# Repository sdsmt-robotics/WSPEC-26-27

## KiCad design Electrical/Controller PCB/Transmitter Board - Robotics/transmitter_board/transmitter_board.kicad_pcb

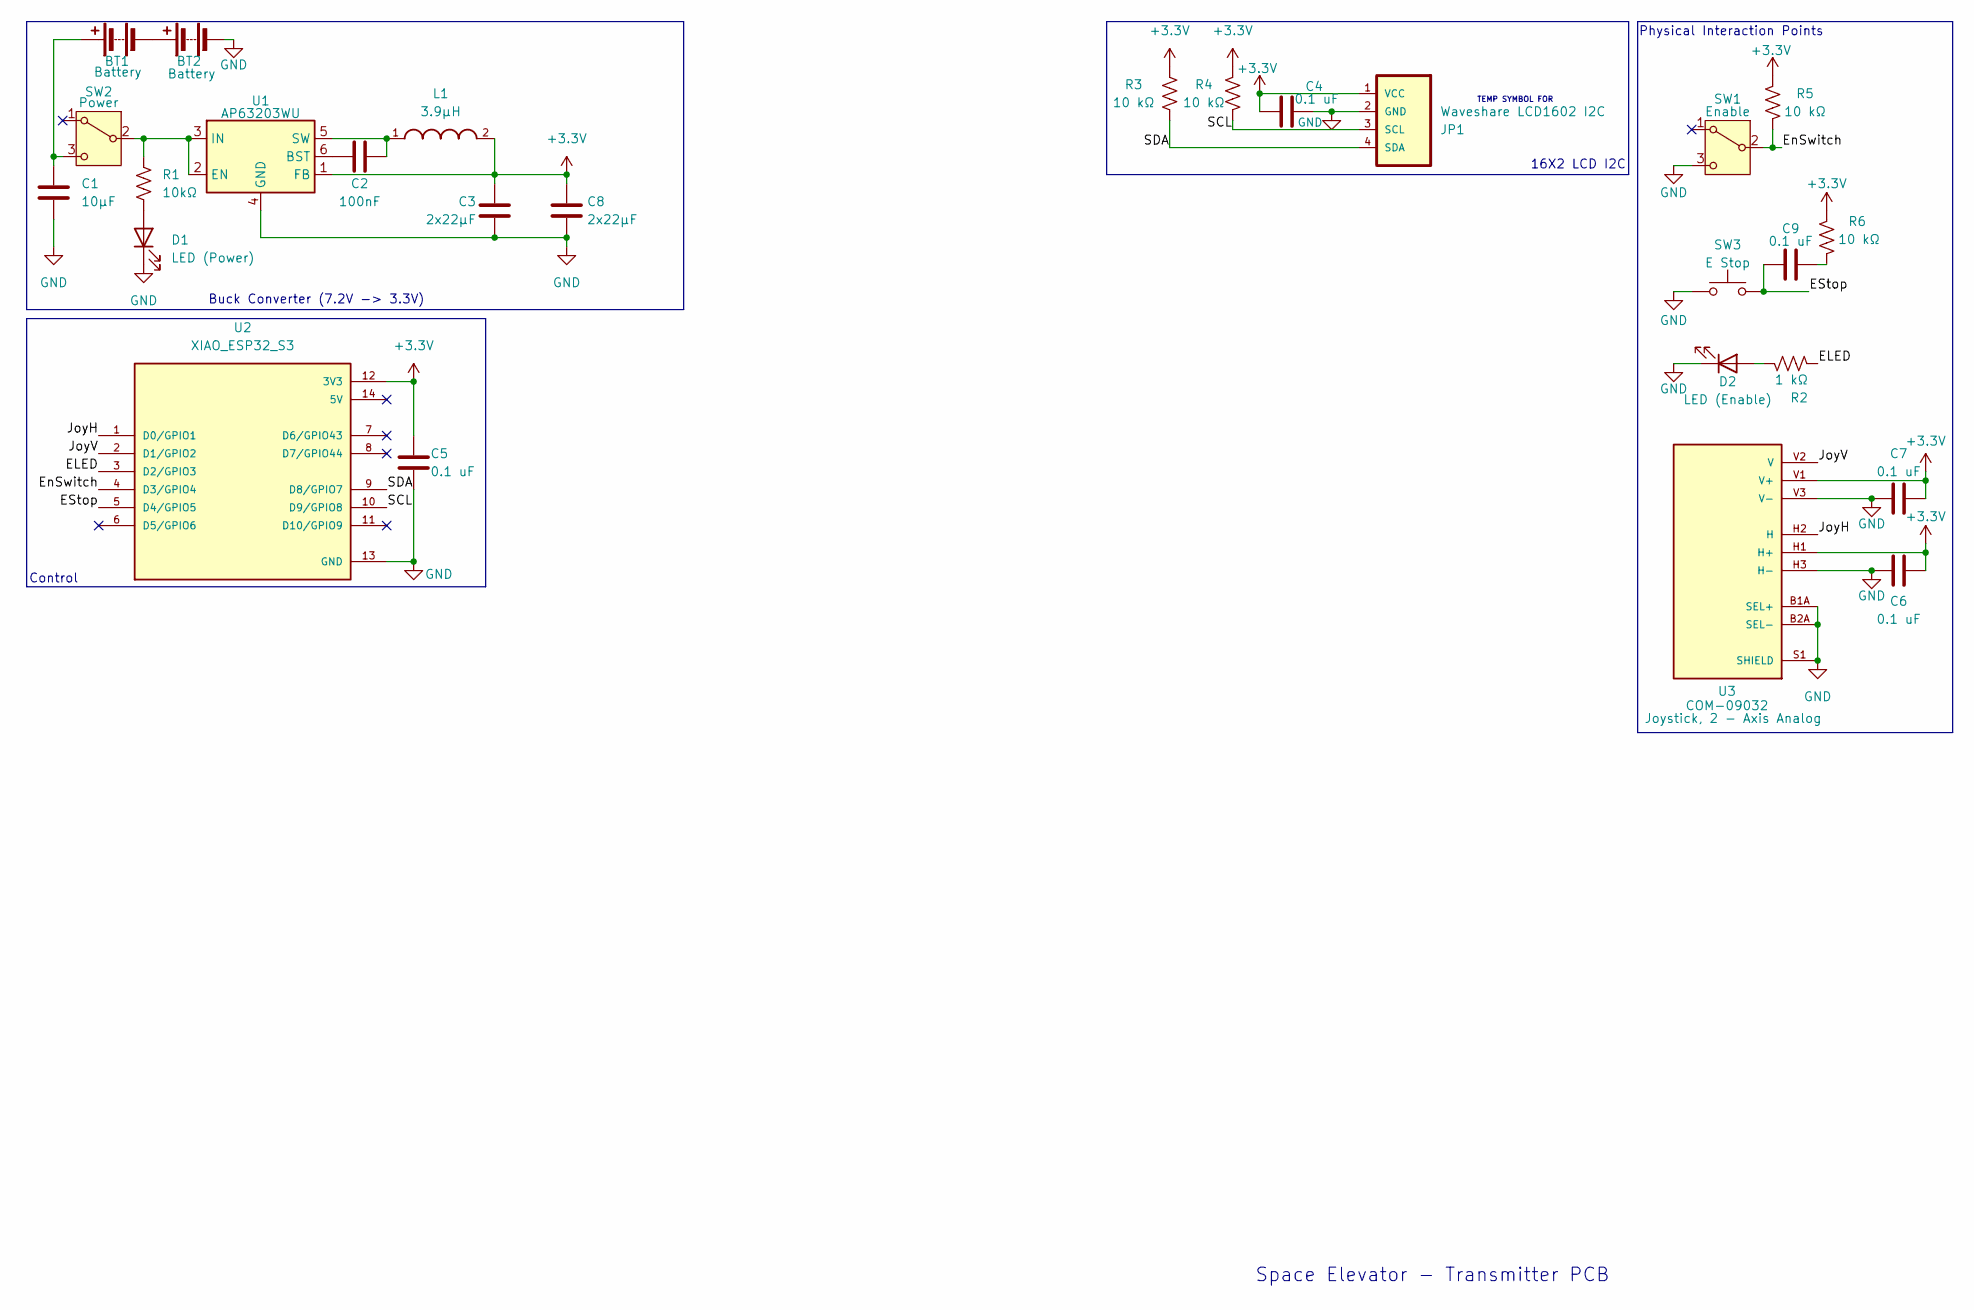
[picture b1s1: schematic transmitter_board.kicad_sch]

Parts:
BT1, BT2: Battery; BatteryHolder_Keystone_1042_1x18650
C1: 10µF; C_0805_2012Metric
C2: 100nF; C_0805_2012Metric
C3, C8: 2x22µF; C_0805_2012Metric
C4, C5, C6, C7, C9: 0.1 uF; C_0805_2012Metric
D1: LED (Power); LED_D4.0mm
D2: LED (Enable); LED_D4.0mm
JP1: Waveshare LCD1602 I2C; JST_PH_S4B-PH-K_1x04_P2.00mm_Horizontal
L1: 3.9µH; INDC0603X33N; DigiKey_Part_Number 490-6730-1-ND
R1: 10kΩ; R_0805_2012Metric
R2: 1 kΩ; R_0805_2012Metric
R3, R4, R5, R6: 10 kΩ; R_0805_2012Metric
SW1: Enable; SS12SDP2_NKK
SW2: Power; SS12SDP2_NKK
SW3: E Stop; SW_800AWSP9M2QE
U1: AP63203WU; TSOT-23-6
U2: XIAO_ESP32_S3; MODULE_XIAO_ESP32_S3; PARTREV April 22nd, 2026
U3: COM-09032; XDCR_COM-09032; PARTREV N/A

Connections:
+3.3V: C3.1, C4.1, C5.1, C6.2, C7.2, C8.1, JP1.1 (VCC), L1.2, R3.2, R4.1, R5.2, R6.2, U1.1 (FB), U2.12 (3V3), U3.H1 (H+), U3.V1 (V+)
/ELED: R2.2, U2.3 (D2/GPIO3)
/EStop: C9.1, SW3.2, U2.5 (D4/GPIO5)
/EnSwitch: R5.1, SW1.2 (B), U2.4 (D3/GPIO4)
/JoyH: U2.1 (D0/GPIO1), U3.H2 (H)
/JoyV: U2.2 (D1/GPIO2), U3.V2 (V)
/SCL: JP1.3 (SCL), R4.2, U2.10 (D9/GPIO8)
/SDA: JP1.4 (SDA), R3.1, U2.9 (D8/GPIO7)
GND: BT2.2 (-), C1.2, C3.2, C4.2, C5.2, C6.1, C7.1, C8.2, D1.1 (K), D2.1 (K), JP1.2 (GND), SW1.3 (C), SW3.1, U1.4 (GND), U2.13 (GND), U3.B1A (SEL+), U3.B2A (SEL-), U3.H3 (H-), U3.S1 (SHIELD), U3.S2 (SHIELD), U3.S3 (SHIELD), U3.S4 (SHIELD), U3.V3 (V-)
unnamed: BT1.1 (+), C1.1, SW2.3 (C)
unnamed: BT1.2 (-), BT2.1 (+)
unnamed: C9.2, R6.1
unnamed: D1.2 (A), R1.2
unnamed: D2.2 (A), R2.1
unnamed: R1.1, SW2.2 (B), U1.2 (EN), U1.3 (IN)
unnamed: C2.1, U1.6 (BST)
unnamed: C2.2, L1.1, U1.5 (SW)

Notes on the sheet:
Physical Interaction Points
16X2 LCD I2C
Buck Converter (7.2V -> 3.3V)
TEMP SYMBOL FOR
Space Elevator - Transmitter PCB
Control

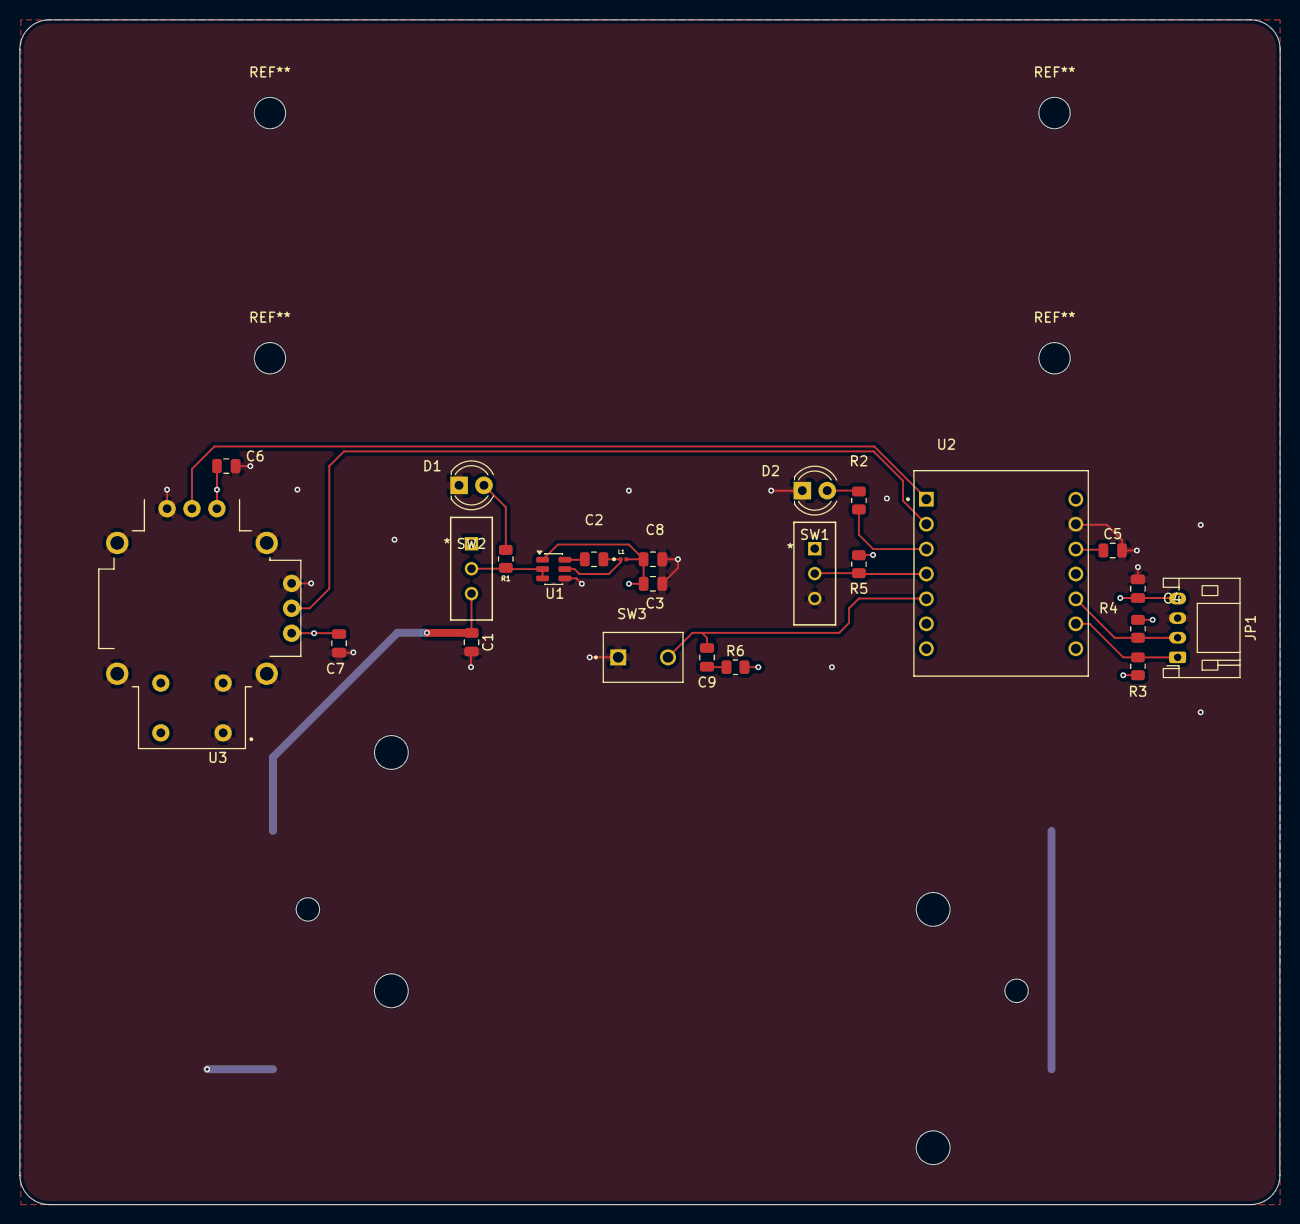
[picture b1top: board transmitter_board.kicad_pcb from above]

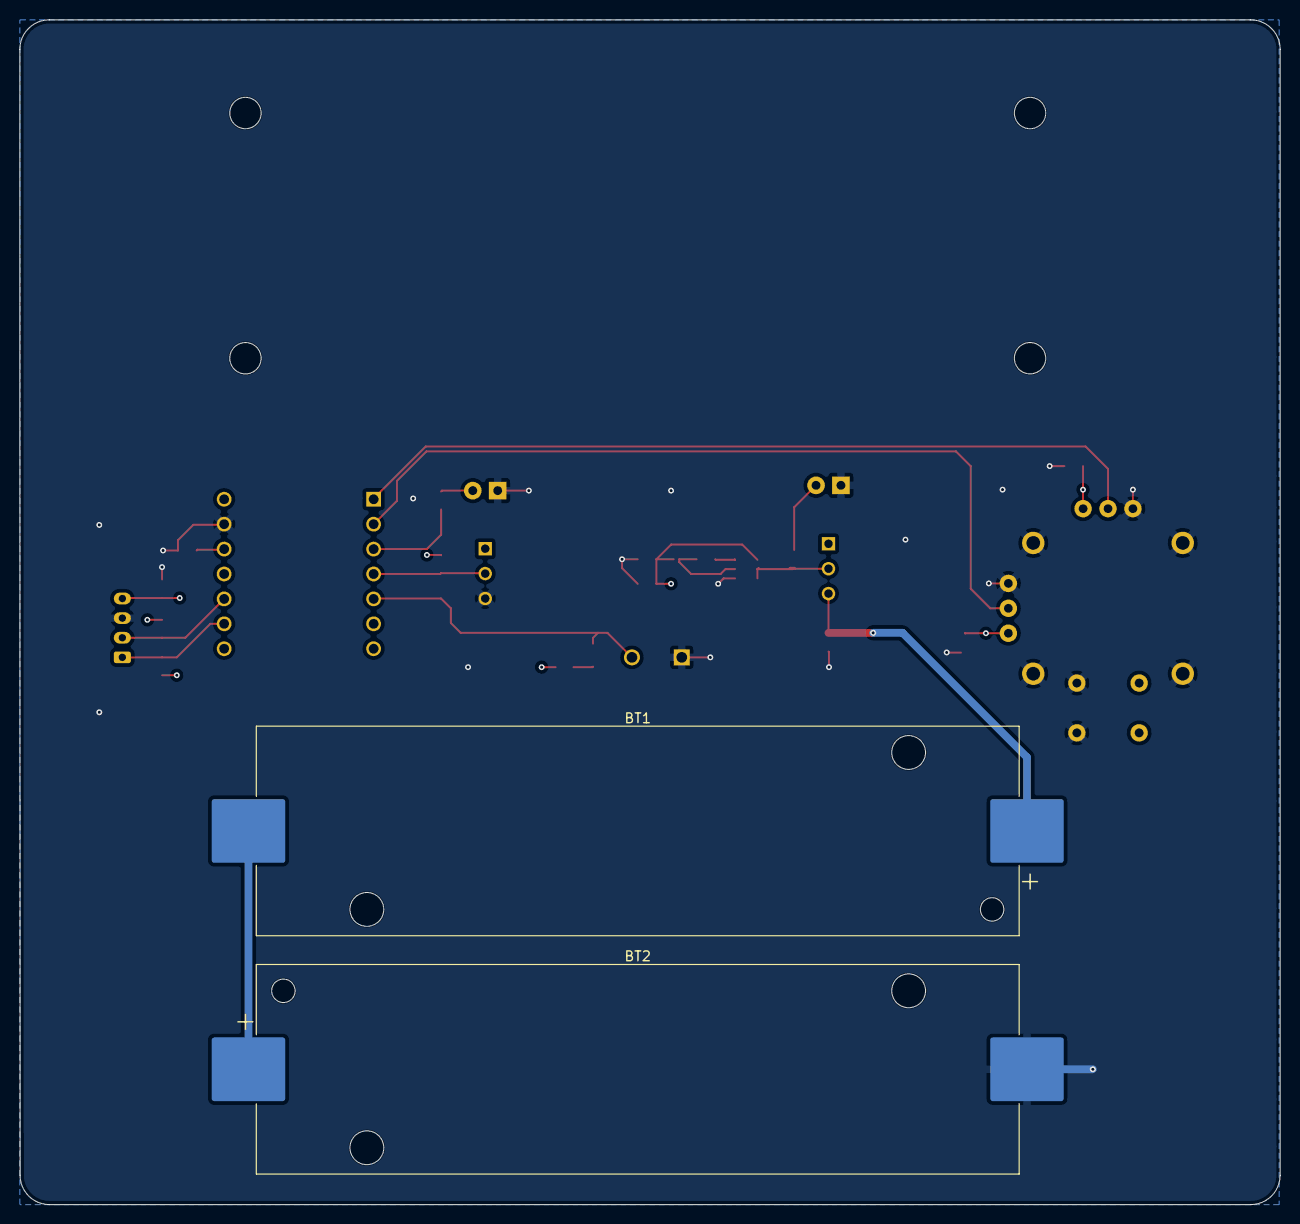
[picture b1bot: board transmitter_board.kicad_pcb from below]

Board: 4 copper layers, 128.5 x 120.8 mm, 27 parts (2 on the bottom side), 17 nets.

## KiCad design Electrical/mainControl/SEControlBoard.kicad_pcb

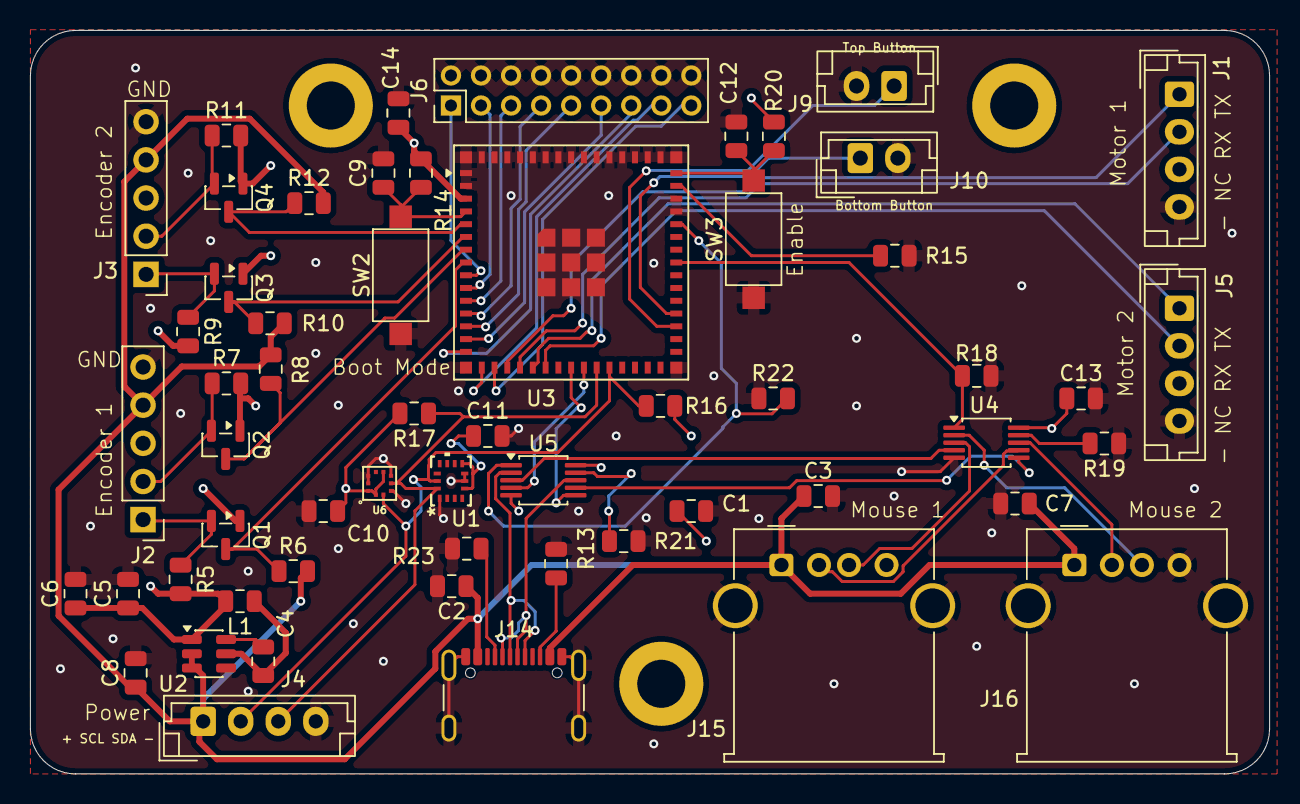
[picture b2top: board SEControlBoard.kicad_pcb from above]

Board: 4 copper layers, 82.5 x 49.5 mm, 57 parts (0 on the bottom side), 49 nets.

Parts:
C1, C2, C3, C4, C7, C8, C9, C10, C11, C12, C13, C14: 100nF; C_0805_2012Metric
C5, C6: 22uF; C_0805_2012Metric
J1, J4, J5: Conn_01x04; JST_EH_B4B-EH-A_1x04_P2.50mm_Vertical
J2: Encoder 1; PinHeader_1x05_P2.54mm_Vertical
J3: Encoder 2; PinHeader_1x05_P2.54mm_Vertical
J6: Conn_02x09_Odd_Even; PinHeader_2x09_P2.00mm_Vertical
J9: TopButton; JST_EH_B2B-EH-A_1x02_P2.50mm_Vertical
J10: BtottomButton; JST_EH_B2B-EH-A_1x02_P2.50mm_Vertical
J14: USB_C_Receptacle_USB2.0_16P; USB_C_Receptacle_GCT_USB4105-xx-A_16P_TopMnt_Horizontal
J15, J16: USB_A; USB_A_Molex_67643_Horizontal
L1: 4.7uH; C_0805_2012Metric
Q1, Q2, Q3, Q4: BSS138; SOT-23
R5, R6, R7, R8, R9, R10, R11, R12, R14, R15, R16, R17, R18, R19, R20, R21, R22: 10k; C_0805_2012Metric
R13, R23: 5.1k; C_0805_2012Metric
SW2, SW3: SW_MEC_5G; SW_SPST_CK_RS282G05A3
U1: BMI323; BMI323_BOS
U2: AP63203WU; TSOT-23-6
U3: ESP32-S3-MINI-1U; ESP32-S2-MINI-1U
U4, U5: TS3USB30EDGSR; TSSOP-10_3x3mm_P0.5mm
U6: BMP384; LGA-10

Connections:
+3.3V: C1.1, C5.1, C6.1, C10.1, C11.1, C13.1, C14.1, L1.2, Q1.1 (G), Q2.1 (G), Q3.1 (G), Q4.1 (G), R5.2, R7.2, R9.2, R11.2, R14.2, R16.2, R17.2, R20.2, U1.5 (VDDIO), U1.8 (VDD), U2.1 (FB), U3.3 (3V3), U4.10 (VCC), U5.10 (VCC), U6.1 (VDDIO), U6.6 (CSB), U6.10 (VDD)
+5V: C2.1, C3.1, C7.1, C8.1, J2.4, J3.4, J4.1, J14.A4 (VBUS), J14.A9 (VBUS), J14.B4 (VBUS), J14.B9 (VBUS), J15.1 (VBUS), J16.1 (VBUS), R6.2, R8.2, R10.2, R12.2, U2.2 (EN), U2.3 (IN)
/BO_1: J6.1, U3.9 (IO5)
/BO_2: J6.3, U3.10 (IO6)
/BO_3: J6.5, U3.11 (IO7)
/BO_4: J6.7, U3.12 (IO8)
/BO_5: J6.9, U3.13 (IO9)
/BO_6: J6.11, U3.14 (IO10)
/BO_7: J6.13, U3.15 (IO11)
/BO_8: J6.15, U3.16 (IO12)
/BO_9: J6.17, U3.17 (IO13)
/Bottom Button: J10.1, U3.34 (IO38)
/E1OutA: J2.2, Q2.2 (S), R7.1
/E1Outb: J2.1, Q1.2 (S), R5.1
/E1OutbL: Q1.3 (D), R6.1, U3.8 (IO4)
/E2OutA: J3.2, Q4.2 (S), R11.1
/E2Outb: J3.1, Q3.2 (S), R9.1
/E2OutbL: Q3.3 (D), R10.1, U3.6 (IO2)
/E3OutbL: Q2.3 (D), R8.1, U3.7 (IO3)
/E4OutbL: Q4.3 (D), R12.1, U3.5 (IO1)
/M1_RX: J1.1, U3.18 (IO14)
/M1_TX: J1.2, U3.19 (IO15)
/M2_RX: J5.1, U3.20 (IO16)
/M2_TX: J5.2, U3.21 (IO17)
/Tob Button: J9.1, U3.33 (IO37)
/USBSel1: R18.2, U3.38 (IO42), U4.1 (S)
/USBSel2: R22.2, U3.41 (IO45), U5.1 (S)
/USBo1+: U4.4 (D+), U5.3 (D2+)
/USBo1-: U4.6 (D-), U5.7 (D2-)
/USBo+: U3.24 (USB_D+), U5.4 (D+)
/USBo-: U3.23 (USB_D-), U5.6 (D-)
/espBoot: C9.1, R14.1, SW2.2 (B), U3.4 (IO0)
/espEn: C12.1, R20.1, SW3.2 (B), U3.45 (EN)
/scl: J4.2, R16.1, U1.13 (SCX), U3.26 (IO26), U6.2 (SCK/SCL)
/sda: J4.3, R17.1, U1.14 (SDX), U3.25 (IO21), U6.4 (SDI/SDA)
/usb1_+: J16.3 (D+), U4.2 (D1+)
/usb1_-: J16.2 (D-), U4.8 (D1-)
/usb2_+: J15.3 (D+), U4.3 (D2+)
/usb2_-: J15.2 (D-), U4.7 (D2-)
/usb3_+: J14.A6 (D+), J14.B6 (D+), U5.2 (D1+)
/usb3_-: J14.A7 (D-), J14.B7 (D-), U5.8 (D1-)
GND: C1.2, C2.2, C3.2, C5.2, C6.2, C7.2, C8.2, C9.2, C10.2, C11.2, C12.2, C13.2, C14.2, J1.4, J2.5, J3.5, J4.4, J5.4, J6.2, J6.4, J6.6, J6.8, J6.10, J6.12, J6.14, J6.16, J6.18, J9.2, J10.2, J14.A1 (GND), J14.A12 (GND), J14.B1 (GND), J14.B12 (GND), J14.SH (SHIELD), J15.4 (GND), J15.SH (Shield), J16.4 (GND), J16.SH (Shield), R13.2, R15.2, R18.1, R19.1, R21.1, R22.1, R23.2, SW2.1 (A), SW3.1 (A), U1.1 (SDO), U1.6 (GNDIO), U1.7 (GND), U2.4 (GND), U3.1 (GND), U3.2 (GND), U3.42 (GND), U3.43 (GND), U3.46 (GND), U3.47 (GND), U3.48 (GND), U3.49 (GND), U3.50 (GND), U3.51 (GND), U3.52 (GND), U3.53 (GND), U3.54 (GND), U3.55 (GND), U3.56 (GND), U3.57 (GND), U3.58 (GND), U3.59 (GND), U3.60 (GND), U3.61 (GND), U3.62 (GND), U3.63 (GND), U3.64 (GND), U3.65 (GND), U4.5 (GND), U5.5 (GND), U6.3 (GND), U6.5 (SDO/ADR), U6.8 (GND), U6.9 (GND)
unnamed: J14.A5 (CC1), R23.1
unnamed: J14.B5 (CC2), R13.1
unnamed: C4.2, U2.6 (BST)
unnamed: C4.1, L1.1, U2.5 (SW)
unnamed: R15.1, U3.44 (IO46)
unnamed: R19.2, U4.9 (~OE)
unnamed: R21.2, U5.9 (~OE)
